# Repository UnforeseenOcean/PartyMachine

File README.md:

# PartyMachine
An open-source Bluetooth speaker made entirely on KiCad

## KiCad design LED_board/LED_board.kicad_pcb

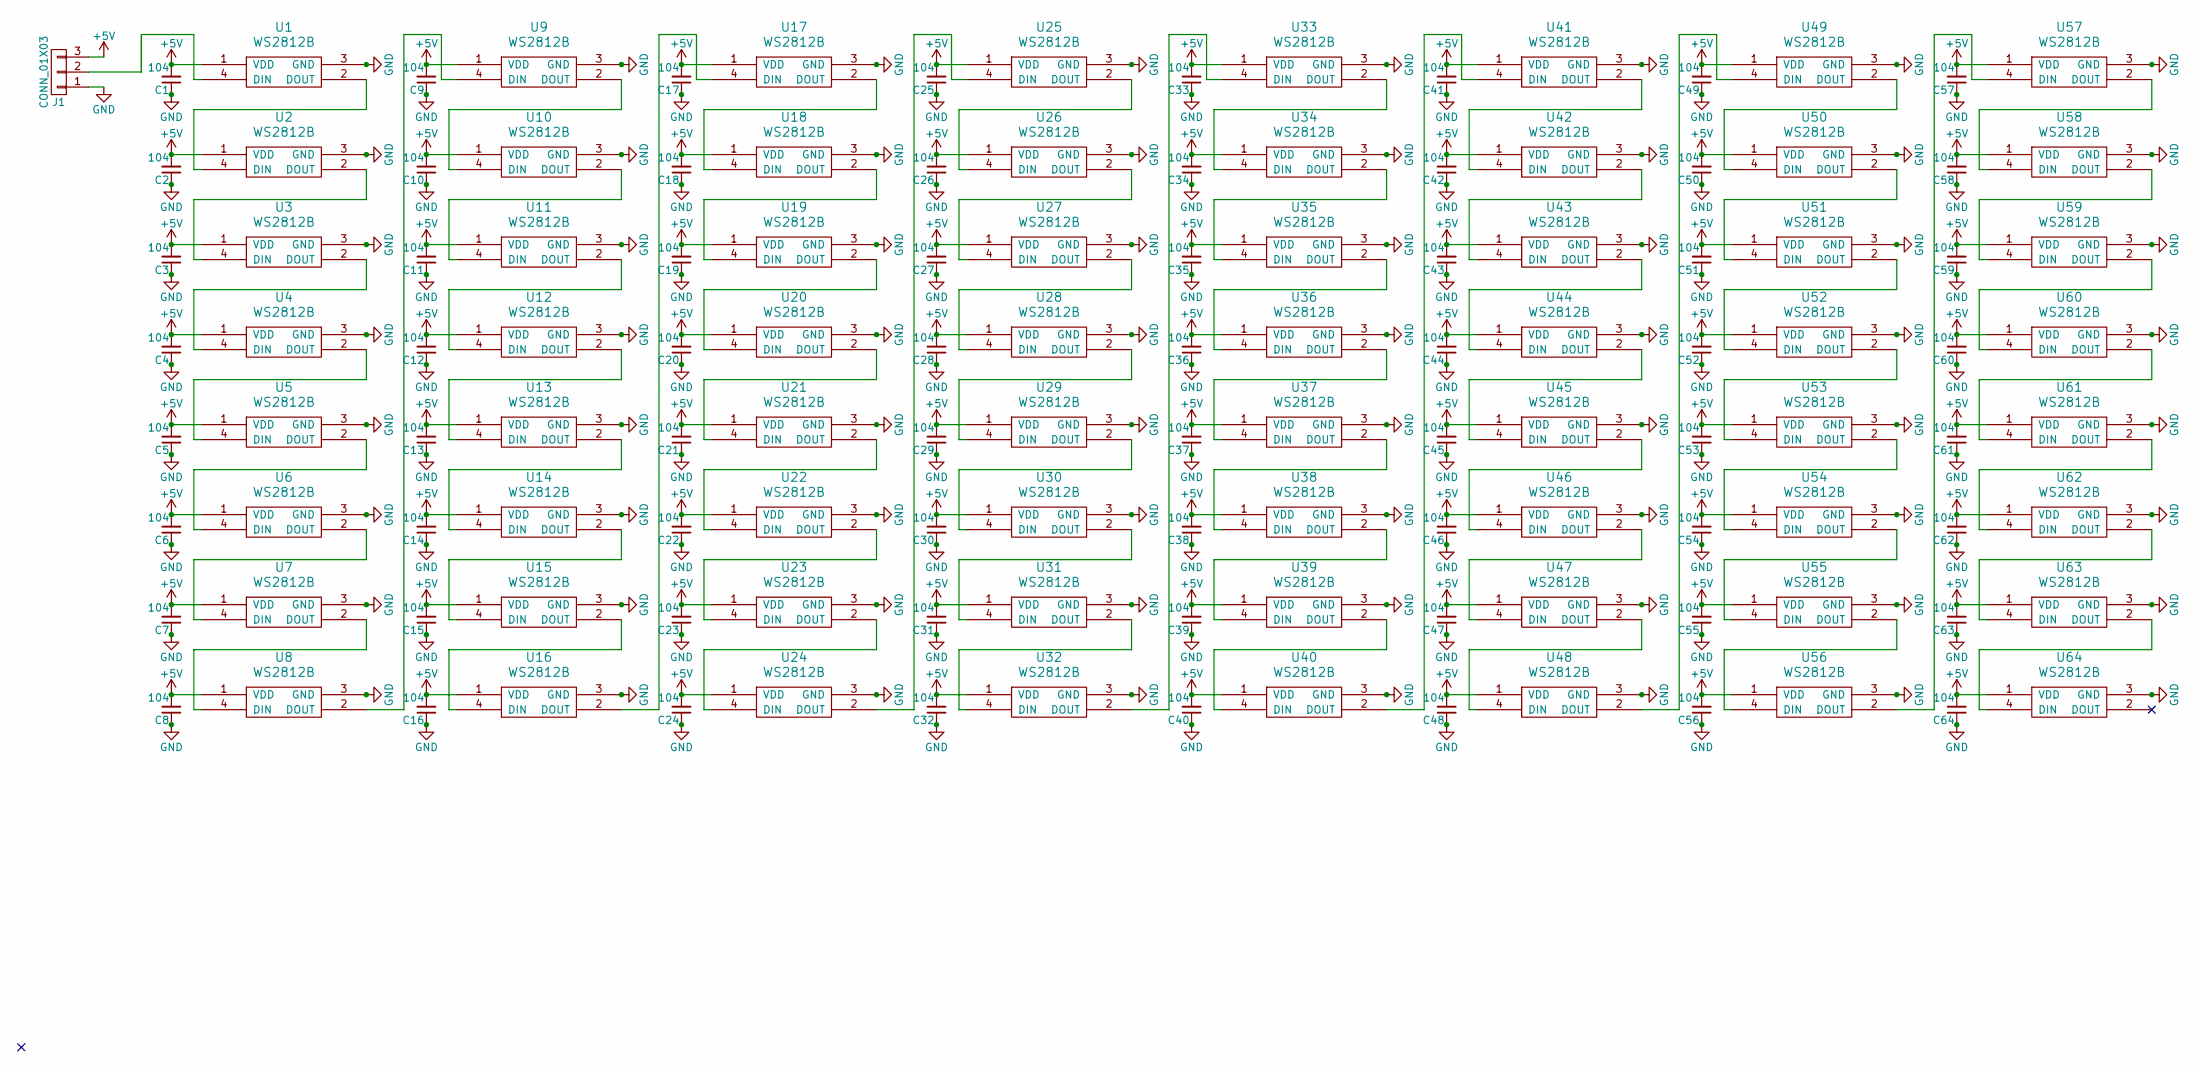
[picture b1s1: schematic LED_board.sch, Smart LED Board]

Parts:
C1, C2, C3, C4, C5, C6, C7, C8, C9, C10, C11, C12, C13, C14, C15, C16, C17, C18, C19, C20, C21, C22, C23, C24, C25, C26, C27, C28, C29, C30, C31, C32, C33, C34, C35, C36, C37, C38, C39, C40, C41, C42, C43, C44, C45, C46, C47, C48, C49, C50, C51, C52, C53, C54, C55, C56, C57, C58, C59, C60, C61, C62, C63, C64: 104; C_0805
J1: CONN_01X03; Pin_Header_Angled_1x03_Pitch2.54mm
U1, U2, U3, U4, U5, U6, U7, U8, U9, U10, U11, U12, U13, U14, U15, U16, U17, U18, U19, U20, U21, U22, U23, U24, U25, U26, U27, U28, U29, U30, U31, U32, U33, U34, U35, U36, U37, U38, U39, U40, U41, U42, U43, U44, U45, U46, U47, U48, U49, U50, U51, U52, U53, U54, U55, U56, U57, U58, U59, U60, U61, U62, U63, U64: WS2812B; LED_WS2812B-PLCC4

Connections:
+5V: C1.2, C2.2, C3.2, C4.2, C5.2, C6.2, C7.2, C8.2, C9.2, C10.2, C11.2, C12.2, C13.2, C14.2, C15.2, C16.2, C17.2, C18.2, C19.2, C20.2, C21.2, C22.2, C23.2, C24.2, C25.2, C26.2, C27.2, C28.2, C29.2, C30.2, C31.2, C32.2, C33.2, C34.2, C35.2, C36.2, C37.2, C38.2, C39.2, C40.2, C41.2, C42.2, C43.2, C44.2, C45.2, C46.2, C47.2, C48.2, C49.2, C50.2, C51.2, C52.2, C53.2, C54.2, C55.2, C56.2, C57.2, C58.2, C59.2, C60.2, C61.2, C62.2, C63.2, C64.2, J1.3, U1.1 (VDD), U2.1 (VDD), U3.1 (VDD), U4.1 (VDD), U5.1 (VDD), U6.1 (VDD), U7.1 (VDD), U8.1 (VDD), U9.1 (VDD), U10.1 (VDD), U11.1 (VDD), U12.1 (VDD), U13.1 (VDD), U14.1 (VDD), U15.1 (VDD), U16.1 (VDD), U17.1 (VDD), U18.1 (VDD), U19.1 (VDD), U20.1 (VDD), U21.1 (VDD), U22.1 (VDD), U23.1 (VDD), U24.1 (VDD), U25.1 (VDD), U26.1 (VDD), U27.1 (VDD), U28.1 (VDD), U29.1 (VDD), U30.1 (VDD), U31.1 (VDD), U32.1 (VDD), U33.1 (VDD), U34.1 (VDD), U35.1 (VDD), U36.1 (VDD), U37.1 (VDD), U38.1 (VDD), U39.1 (VDD), U40.1 (VDD), U41.1 (VDD), U42.1 (VDD), U43.1 (VDD), U44.1 (VDD), U45.1 (VDD), U46.1 (VDD), U47.1 (VDD), U48.1 (VDD), U49.1 (VDD), U50.1 (VDD), U51.1 (VDD), U52.1 (VDD), U53.1 (VDD), U54.1 (VDD), U55.1 (VDD), U56.1 (VDD), U57.1 (VDD), U58.1 (VDD), U59.1 (VDD), U60.1 (VDD), U61.1 (VDD), U62.1 (VDD), U63.1 (VDD), U64.1 (VDD)
GND: C1.1, C2.1, C3.1, C4.1, C5.1, C6.1, C7.1, C8.1, C9.1, C10.1, C11.1, C12.1, C13.1, C14.1, C15.1, C16.1, C17.1, C18.1, C19.1, C20.1, C21.1, C22.1, C23.1, C24.1, C25.1, C26.1, C27.1, C28.1, C29.1, C30.1, C31.1, C32.1, C33.1, C34.1, C35.1, C36.1, C37.1, C38.1, C39.1, C40.1, C41.1, C42.1, C43.1, C44.1, C45.1, C46.1, C47.1, C48.1, C49.1, C50.1, C51.1, C52.1, C53.1, C54.1, C55.1, C56.1, C57.1, C58.1, C59.1, C60.1, C61.1, C62.1, C63.1, C64.1, J1.1, U1.3 (GND), U2.3 (GND), U3.3 (GND), U4.3 (GND), U5.3 (GND), U6.3 (GND), U7.3 (GND), U8.3 (GND), U9.3 (GND), U10.3 (GND), U11.3 (GND), U12.3 (GND), U13.3 (GND), U14.3 (GND), U15.3 (GND), U16.3 (GND), U17.3 (GND), U18.3 (GND), U19.3 (GND), U20.3 (GND), U21.3 (GND), U22.3 (GND), U23.3 (GND), U24.3 (GND), U25.3 (GND), U26.3 (GND), U27.3 (GND), U28.3 (GND), U29.3 (GND), U30.3 (GND), U31.3 (GND), U32.3 (GND), U33.3 (GND), U34.3 (GND), U35.3 (GND), U36.3 (GND), U37.3 (GND), U38.3 (GND), U39.3 (GND), U40.3 (GND), U41.3 (GND), U42.3 (GND), U43.3 (GND), U44.3 (GND), U45.3 (GND), U46.3 (GND), U47.3 (GND), U48.3 (GND), U49.3 (GND), U50.3 (GND), U51.3 (GND), U52.3 (GND), U53.3 (GND), U54.3 (GND), U55.3 (GND), U56.3 (GND), U57.3 (GND), U58.3 (GND), U59.3 (GND), U60.3 (GND), U61.3 (GND), U62.3 (GND), U63.3 (GND), U64.3 (GND)
unnamed: J1.2, U1.4 (DIN)
unnamed: U1.2 (DOUT), U2.4 (DIN)
unnamed: U2.2 (DOUT), U3.4 (DIN)
unnamed: U3.2 (DOUT), U4.4 (DIN)
unnamed: U4.2 (DOUT), U5.4 (DIN)
unnamed: U5.2 (DOUT), U6.4 (DIN)
unnamed: U6.2 (DOUT), U7.4 (DIN)
unnamed: U7.2 (DOUT), U8.4 (DIN)
unnamed: U8.2 (DOUT), U9.4 (DIN)
unnamed: U10.2 (DOUT), U11.4 (DIN)
unnamed: U9.2 (DOUT), U10.4 (DIN)
unnamed: U11.2 (DOUT), U12.4 (DIN)
unnamed: U12.2 (DOUT), U13.4 (DIN)
unnamed: U13.2 (DOUT), U14.4 (DIN)
unnamed: U14.2 (DOUT), U15.4 (DIN)
unnamed: U15.2 (DOUT), U16.4 (DIN)
unnamed: U16.2 (DOUT), U17.4 (DIN)
unnamed: U17.2 (DOUT), U18.4 (DIN)
unnamed: U18.2 (DOUT), U19.4 (DIN)
unnamed: U19.2 (DOUT), U20.4 (DIN)
unnamed: U20.2 (DOUT), U21.4 (DIN)
unnamed: U21.2 (DOUT), U22.4 (DIN)
unnamed: U22.2 (DOUT), U23.4 (DIN)
unnamed: U23.2 (DOUT), U24.4 (DIN)
unnamed: U24.2 (DOUT), U25.4 (DIN)
unnamed: U25.2 (DOUT), U26.4 (DIN)
unnamed: U26.2 (DOUT), U27.4 (DIN)
unnamed: U27.2 (DOUT), U28.4 (DIN)
unnamed: U28.2 (DOUT), U29.4 (DIN)
unnamed: U29.2 (DOUT), U30.4 (DIN)
unnamed: U30.2 (DOUT), U31.4 (DIN)
unnamed: U31.2 (DOUT), U32.4 (DIN)
unnamed: U32.2 (DOUT), U33.4 (DIN)
unnamed: U33.2 (DOUT), U34.4 (DIN)
unnamed: U34.2 (DOUT), U35.4 (DIN)
unnamed: U35.2 (DOUT), U36.4 (DIN)
unnamed: U36.2 (DOUT), U37.4 (DIN)
unnamed: U37.2 (DOUT), U38.4 (DIN)
unnamed: U38.2 (DOUT), U39.4 (DIN)
unnamed: U39.2 (DOUT), U40.4 (DIN)
unnamed: U40.2 (DOUT), U41.4 (DIN)
unnamed: U41.2 (DOUT), U42.4 (DIN)
unnamed: U42.2 (DOUT), U43.4 (DIN)
unnamed: U43.2 (DOUT), U44.4 (DIN)
unnamed: U44.2 (DOUT), U45.4 (DIN)
unnamed: U45.2 (DOUT), U46.4 (DIN)
unnamed: U46.2 (DOUT), U47.4 (DIN)
unnamed: U47.2 (DOUT), U48.4 (DIN)
unnamed: U48.2 (DOUT), U49.4 (DIN)
unnamed: U49.2 (DOUT), U50.4 (DIN)
unnamed: U50.2 (DOUT), U51.4 (DIN)
unnamed: U51.2 (DOUT), U52.4 (DIN)
unnamed: U52.2 (DOUT), U53.4 (DIN)
unnamed: U53.2 (DOUT), U54.4 (DIN)
unnamed: U54.2 (DOUT), U55.4 (DIN)
unnamed: U55.2 (DOUT), U56.4 (DIN)
unnamed: U56.2 (DOUT), U57.4 (DIN)
unnamed: U57.2 (DOUT), U58.4 (DIN)
unnamed: U58.2 (DOUT), U59.4 (DIN)
unnamed: U59.2 (DOUT), U60.4 (DIN)
unnamed: U60.2 (DOUT), U61.4 (DIN)
unnamed: U61.2 (DOUT), U62.4 (DIN)
unnamed: U62.2 (DOUT), U63.4 (DIN)
unnamed: U63.2 (DOUT), U64.4 (DIN)

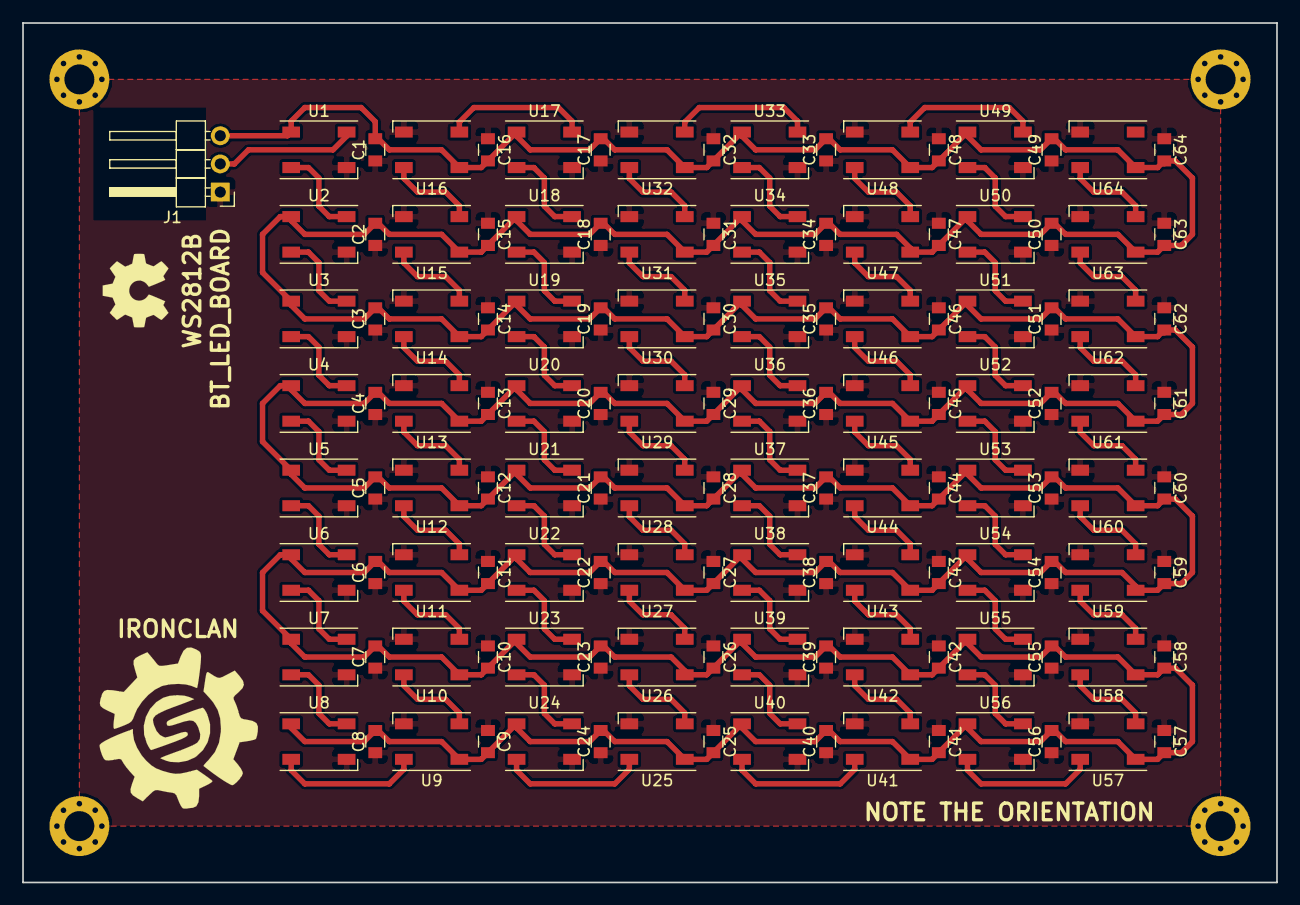
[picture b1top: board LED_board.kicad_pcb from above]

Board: 2 copper layers, 113.0 x 77.5 mm, 129 parts (0 on the bottom side), 66 nets.
